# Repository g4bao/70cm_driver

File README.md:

# 70cm_driver
Details of a 70cm driver kit inspired by the original G4BAO 23cm driver project
The decision has been made to not sell any further kits so the designs are now made available here under the terms of an MIT licence. It includes a copy of the original article, Eagle board and schematic files, plus Gerber files for the PCB, which must be made from FR4 0.7mm substrate.
Contains Schematics and PCB layout as image files plus Eagle 7 board and schematic files
Contains Gerber files for the latest v1.1 PCB
Contains images from the tests done by BATC and written up in their house magazine

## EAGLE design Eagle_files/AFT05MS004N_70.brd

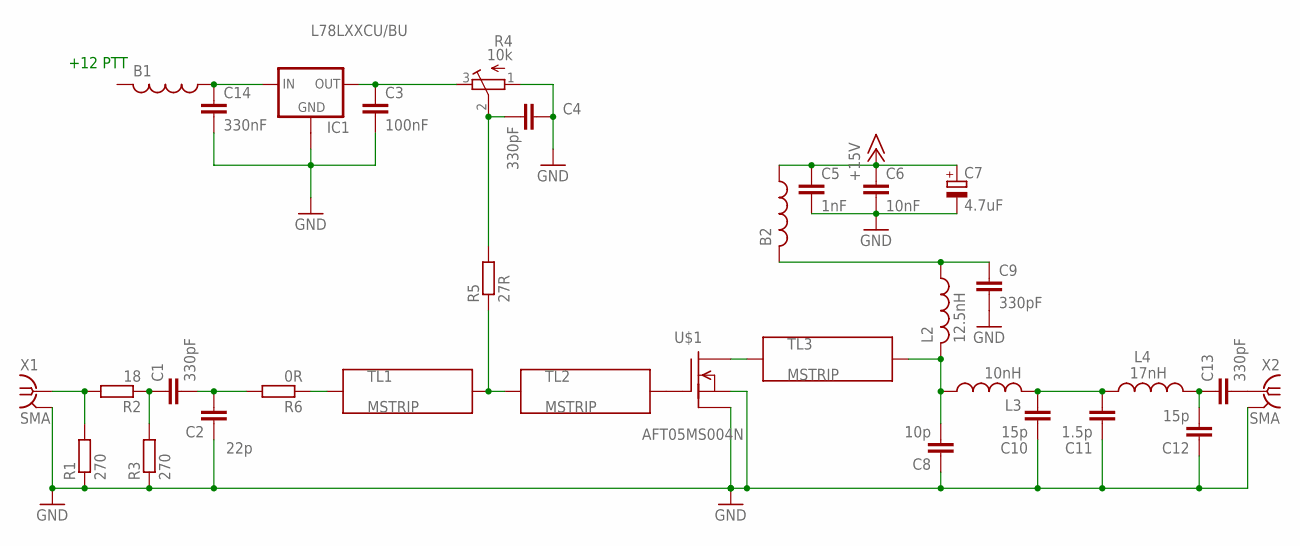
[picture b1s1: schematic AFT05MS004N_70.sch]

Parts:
B1, B2: L-US0204/5; 0204/5
C1, C13: 330pF; C0805
C2: 22p; C0603
C3: 100nF; C0805
C4, C9: 330pF; C0603
C5: 1nF; C0603
C6: 10nF; C0805
C7: 4.7uF; SANYO-OSCON_SMD_B6
C8: 10p; C0603
C10, C12: 15p; C0603
C11: 1.5p; C0603
C14: 330nF; C0805
IC1: L78LXXCU/BU; SOT89
L2: 12.5nH; 0805
L3: 10nH; 0805
L4: 17nH; 0805
R1, R3: 270; R0603
R2: 18; R0603
R4: 10k; RTRIM3214W
R5: 27R; R0603
R6: 0R; R0603
TL1, TL2, TL3: MSTRIP; TRLINE2
U$1: AFT05MS004N; SOT-89
X1, X2: SMA; J502-ND-142-0711-871/876

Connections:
+13.6: B2.1, C5.1, C6.1, C7.+
GND: C2.1, C3.2, C4.1, C5.2, C6.2, C7.-, C8.1, C9.2, C10.1, C11.1, C12.1, C14.2, IC1.4 (GND1), R1.1, R3.1, R4.1 (E), U$1.2 (S), U$1.2@1 (S1), X1.G@1 (GND), X1.G@2 (GND), X1.G@3 (GND), X1.G@4 (GND), X2.G@1 (GND), X2.G@2 (GND), X2.G@3 (GND), X2.G@4 (GND)
unnamed: R1.2, R2.2, X1.1
unnamed: B2.2, C9.1, L2.1
unnamed: C13.2, X2.1
unnamed: R6.1, TL1.P$1 (1)
unnamed: C4.2, R4.2 (S), R5.2
unnamed: C8.2, L2.2, L3.1, TL3.P$2 (2)
unnamed: B1.1, C14.1, IC1.3 (IN)
unnamed: C1.2, C2.2, R6.2
unnamed: C3.1, IC1.1 (OUT), R4.3 (A)
unnamed: C10.2, C11.2, L3.2, L4.1
unnamed: C12.2, C13.1, L4.2
unnamed: C1.1, R2.1, R3.2
unnamed: TL2.P$2 (2), U$1.1 (G)
unnamed: R5.1, TL1.P$2 (2), TL2.P$1 (1)
unnamed: TL3.P$1 (1), U$1.3 (D)

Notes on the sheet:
+12 PTT

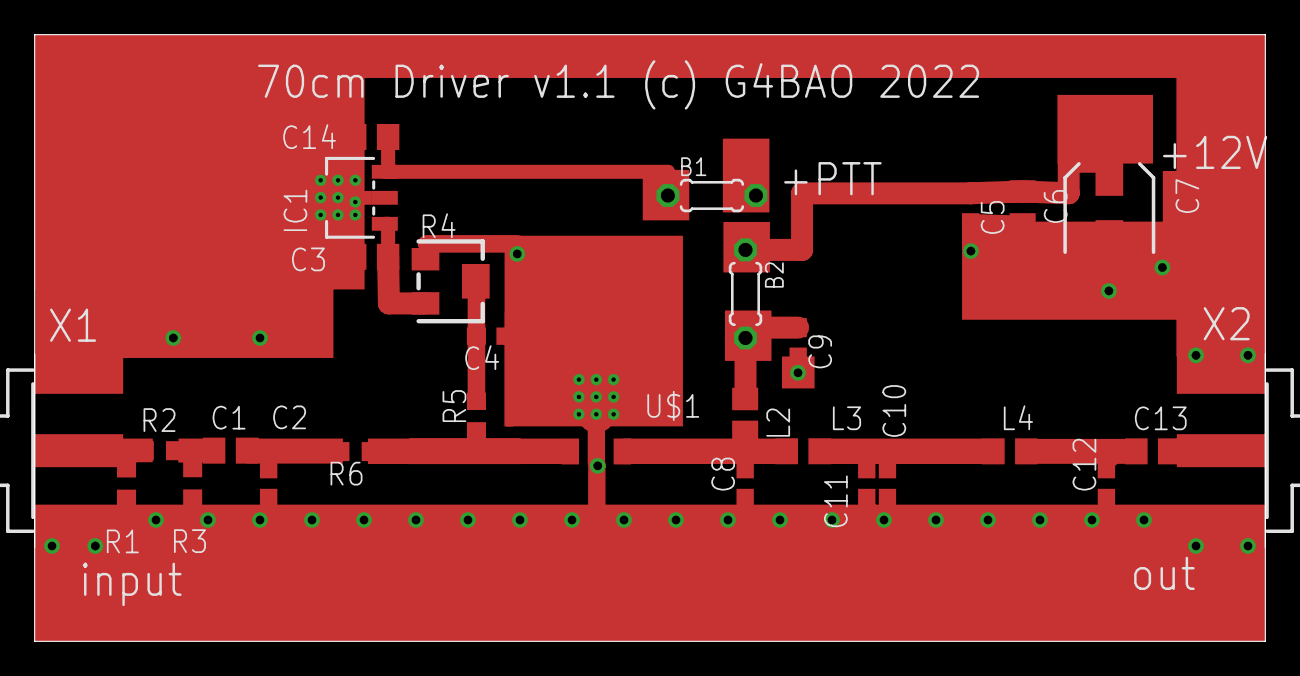
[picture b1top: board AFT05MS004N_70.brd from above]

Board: 2 copper layers, 71.0 x 35.0 mm, 32 parts (0 on the bottom side), 17 nets.
